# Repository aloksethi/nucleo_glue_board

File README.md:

# Nucleo Glue Board

A small pcb which sits on top of NUCLEO-F429ZI board.
It connects to the two morpho connectors (CN12 and CN11) and provides a handy way to connect to the power and RF board.
also provides 4 reference currents

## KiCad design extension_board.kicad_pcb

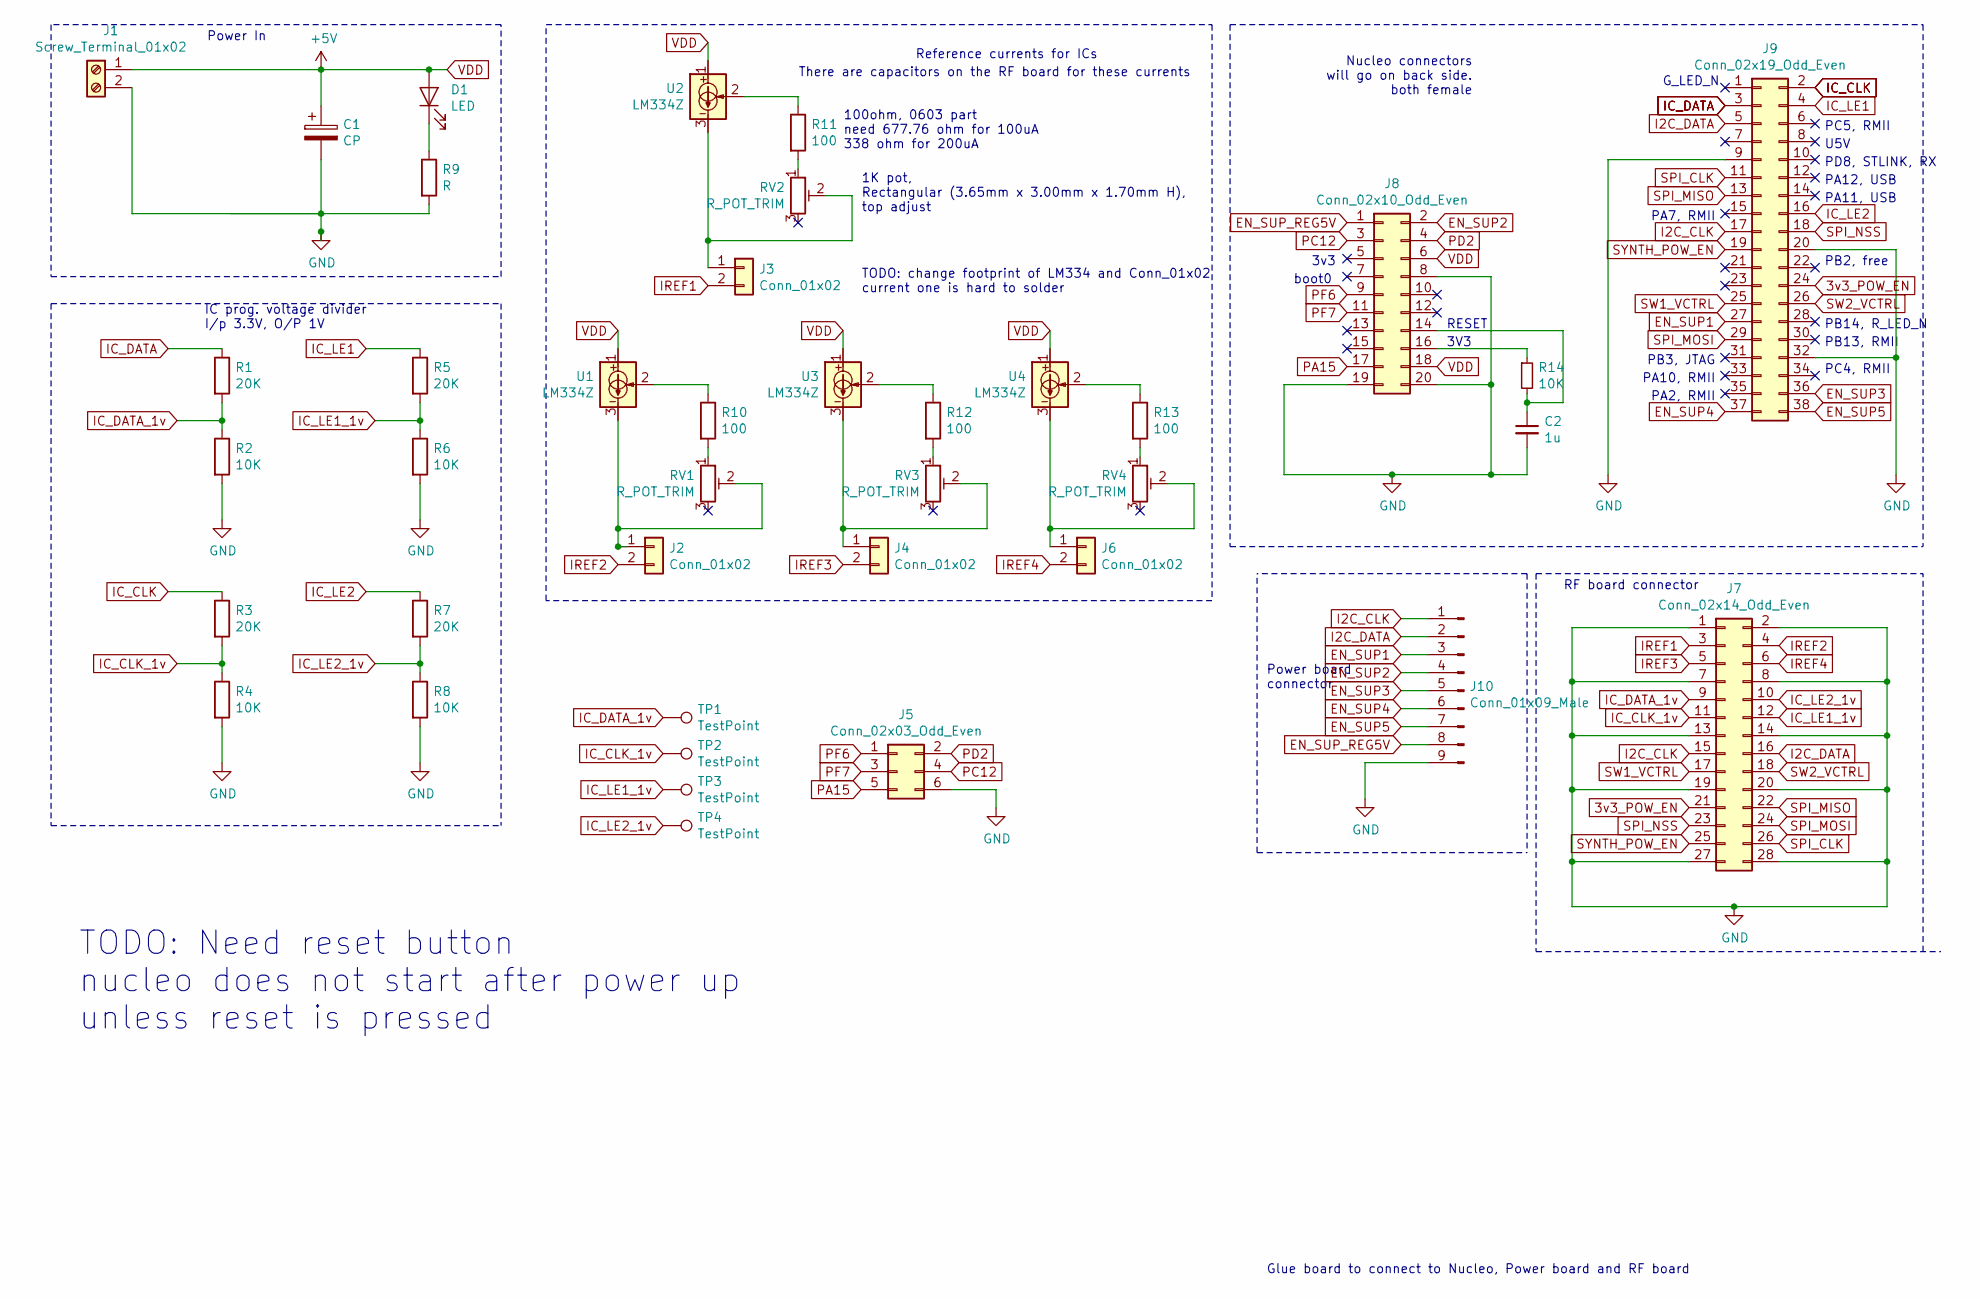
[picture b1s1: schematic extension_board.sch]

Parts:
C1: CP; CP_Elec_4x5.8
C2: 1u; C_0805_2012Metric_Pad1.15x1.40mm_HandSolder
D1: LED; LED_0805_2012Metric_Pad1.15x1.40mm_HandSolder
J1: Screw_Terminal_01x02; Term_Block_1x2_P5.08MM
J2, J3, J4, J6: Conn_01x02; PinHeader_1x02_P2.54mm_Vertical
J5: Conn_02x03_Odd_Even; PinHeader_2x03_P2.54mm_Vertical_SMD
J7: Conn_02x14_Odd_Even; PinHeader_2x14_P2.54mm_Vertical_SMD
J8: Conn_02x10_Odd_Even; PinHeader_2x10_P2.54mm_Vertical
J9: Conn_02x19_Odd_Even; PinHeader_2x19_P2.54mm_Vertical
J10: Conn_01x09_Male; PinHeader_1x09_P2.54mm_Vertical_SMD_Pin1Left
R1, R3, R5, R7: 20K; R_0805_2012Metric_Pad1.15x1.40mm_HandSolder
R2, R4, R6, R8, R14: 10K; R_0805_2012Metric_Pad1.15x1.40mm_HandSolder
R9: R; R_0805_2012Metric_Pad1.15x1.40mm_HandSolder
R10, R11, R12, R13: 100; R_0603_1608Metric_Pad1.05x0.95mm_HandSolder
RV1, RV2, RV3, RV4: R_POT_TRIM; Trimpot_3.8mmx3.6mm_TC33X-2-103E
TP1, TP2, TP3, TP4: TestPoint; TestPoint_Pad_1.0x1.0mm
U1, U2, U3, U4: LM334Z; TO-92_Inline_Wide

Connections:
3v3_POW_EN: J7.21, J9.24
EN_SUP1: J9.27, J10.3
EN_SUP2: J8.2, J10.4
EN_SUP3: J9.36, J10.5
EN_SUP4: J9.37, J10.6
EN_SUP5: J9.38, J10.7
EN_SUP_REG5V: J8.1, J10.8
GND: C1.2, C2.2, J1.2, J5.6, J7.1, J7.2, J7.7, J7.8, J7.13, J7.14, J7.19, J7.20, J7.27, J7.28, J8.8, J8.19, J8.20, J9.9, J9.20, J9.32, J10.9, R2.2, R4.2, R6.2, R8.2, R9.2
I2C_CLK: J7.15, J9.17, J10.1
I2C_DATA: J7.16, J9.5, J10.2
IC_CLK: J9.2, R3.1
IC_CLK_1v: J7.11, R3.2, R4.1, TP2.1
IC_DATA: J9.3, R1.1
IC_DATA_1v: J7.9, R1.2, R2.1, TP1.1
IC_LE1: J9.4, R5.1
IC_LE1_1v: J7.12, R5.2, R6.1, TP3.1
IC_LE2: J9.16, R7.1
IC_LE2_1v: J7.10, R7.2, R8.1, TP4.1
IREF1: J3.2, J7.3
IREF2: J2.2, J7.4
IREF3: J4.2, J7.5
IREF4: J6.2, J7.6
unnamed: C2.1, J8.14, R14.2
unnamed: D1.1 (K), R9.1
unnamed: J2.1, RV1.2, U1.3
unnamed: J3.1, RV2.2, U2.3
unnamed: J4.1, RV3.2, U3.3
unnamed: J6.1, RV4.2, U4.3
unnamed: J8.16, R14.1
unnamed: R10.1, U1.2
unnamed: R10.2, RV1.1
unnamed: R11.1, U2.2
unnamed: R11.2, RV2.1
unnamed: R12.1, U3.2
unnamed: R12.2, RV3.1
unnamed: R13.1, U4.2
unnamed: R13.2, RV4.1
PA15: J5.5, J8.17
PC12: J5.4, J8.3
PD2: J5.2, J8.4
PF6: J5.1, J8.9
PF7: J5.3, J8.11
SPI_CLK: J7.26, J9.11
SPI_MISO: J7.22, J9.13
SPI_MOSI: J7.24, J9.29
SPI_NSS: J7.23, J9.18
SW1_VCTRL: J7.17, J9.25
SW2_VCTRL: J7.18, J9.26
SYNTH_POW_EN: J7.25, J9.19
VDD: C1.1, D1.2 (A), J1.1, J8.6, J8.18, U1.1, U2.1, U3.1, U4.1

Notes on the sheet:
Glue board to connect to Nucleo, Power board and RF board
Power In
Nucleo connectors will go on back side. both female
RF board connector
IC prog. voltage divider I/p 3.3V, O/P 1V
100ohm, 0603 part need 677.76 ohm for 100uA 338 ohm for 200uA
1K pot, Rectangular (3.65mm x 3.00mm x 1.70mm H), top adjust
Power board connector
PC5, RMII
U5V
PD8, STLINK, RX
PA12, USB
PA11, USB
PB2, free
PB14, R_LED_N
G_LED_N
PB13, RMII
PC4, RMII
PA2, RMII
PA10, RMII
PB3, JTAG
PA7, RMII
3v3
boot0
Reference currents for ICs
There are capacitors on the RF board for these currents
TODO: change footprint of LM334 and Conn_01x02 current one is hard to solder
TODO: Need reset button nucleo does not start after power up unless reset is pressed
RESET
3V3

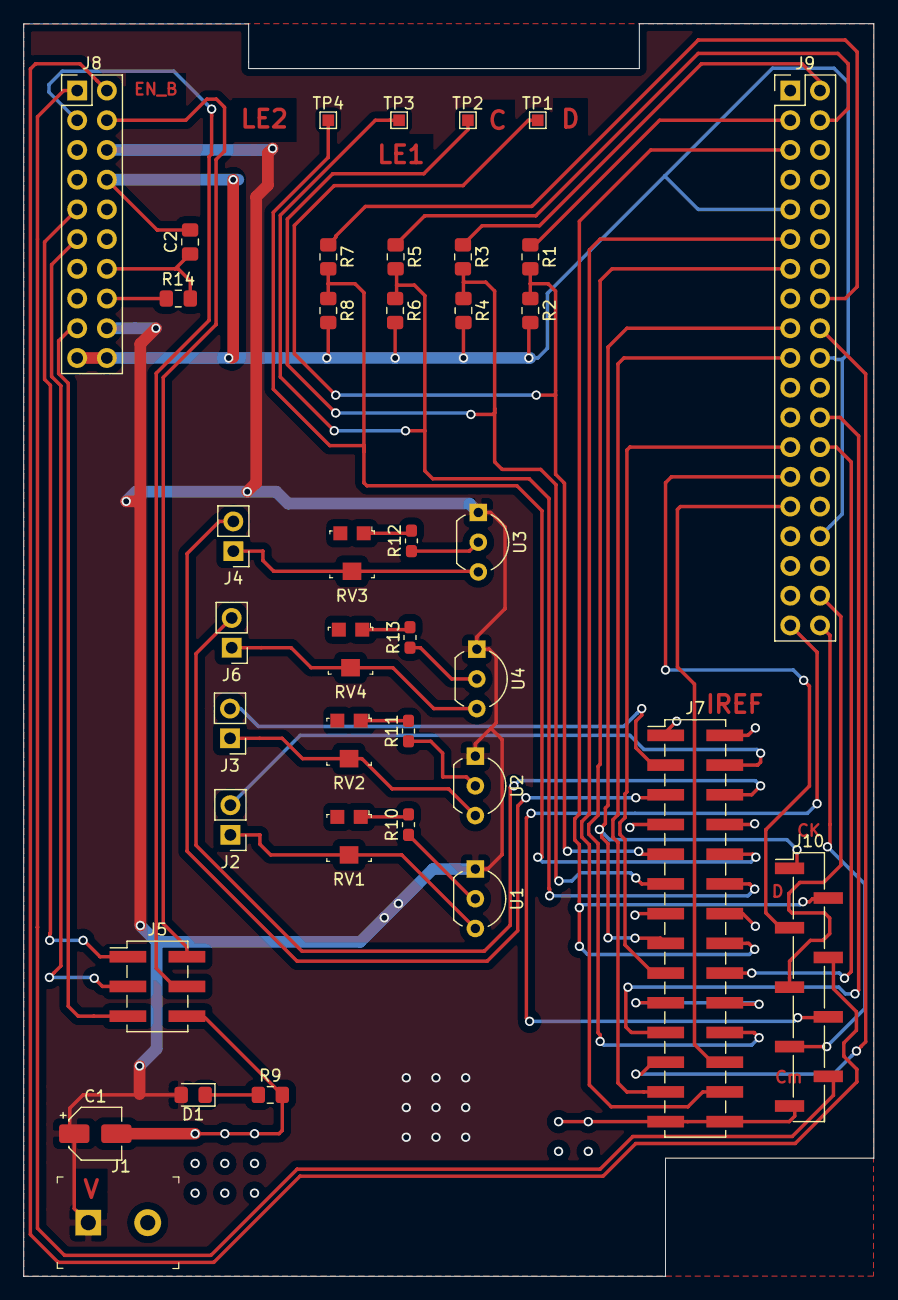
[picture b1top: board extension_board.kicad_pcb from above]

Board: 2 copper layers, 72.7 x 107.1 mm, 39 parts (0 on the bottom side), 50 nets.

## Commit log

2021-03-12 initial design
2021-03-15 adding digikey libraries as submodule
2021-03-16 first version of the pcb
2021-03-16 added labels on Top copper
2021-03-16 added gerber files
2021-04-13 had shorted gnd and AVDD on the cn12 connector
2021-06-20 changed footprint assignments, added reset circuit
2021-06-22 gerber files and final files
2021-08-13 gerber filex for second pcb
